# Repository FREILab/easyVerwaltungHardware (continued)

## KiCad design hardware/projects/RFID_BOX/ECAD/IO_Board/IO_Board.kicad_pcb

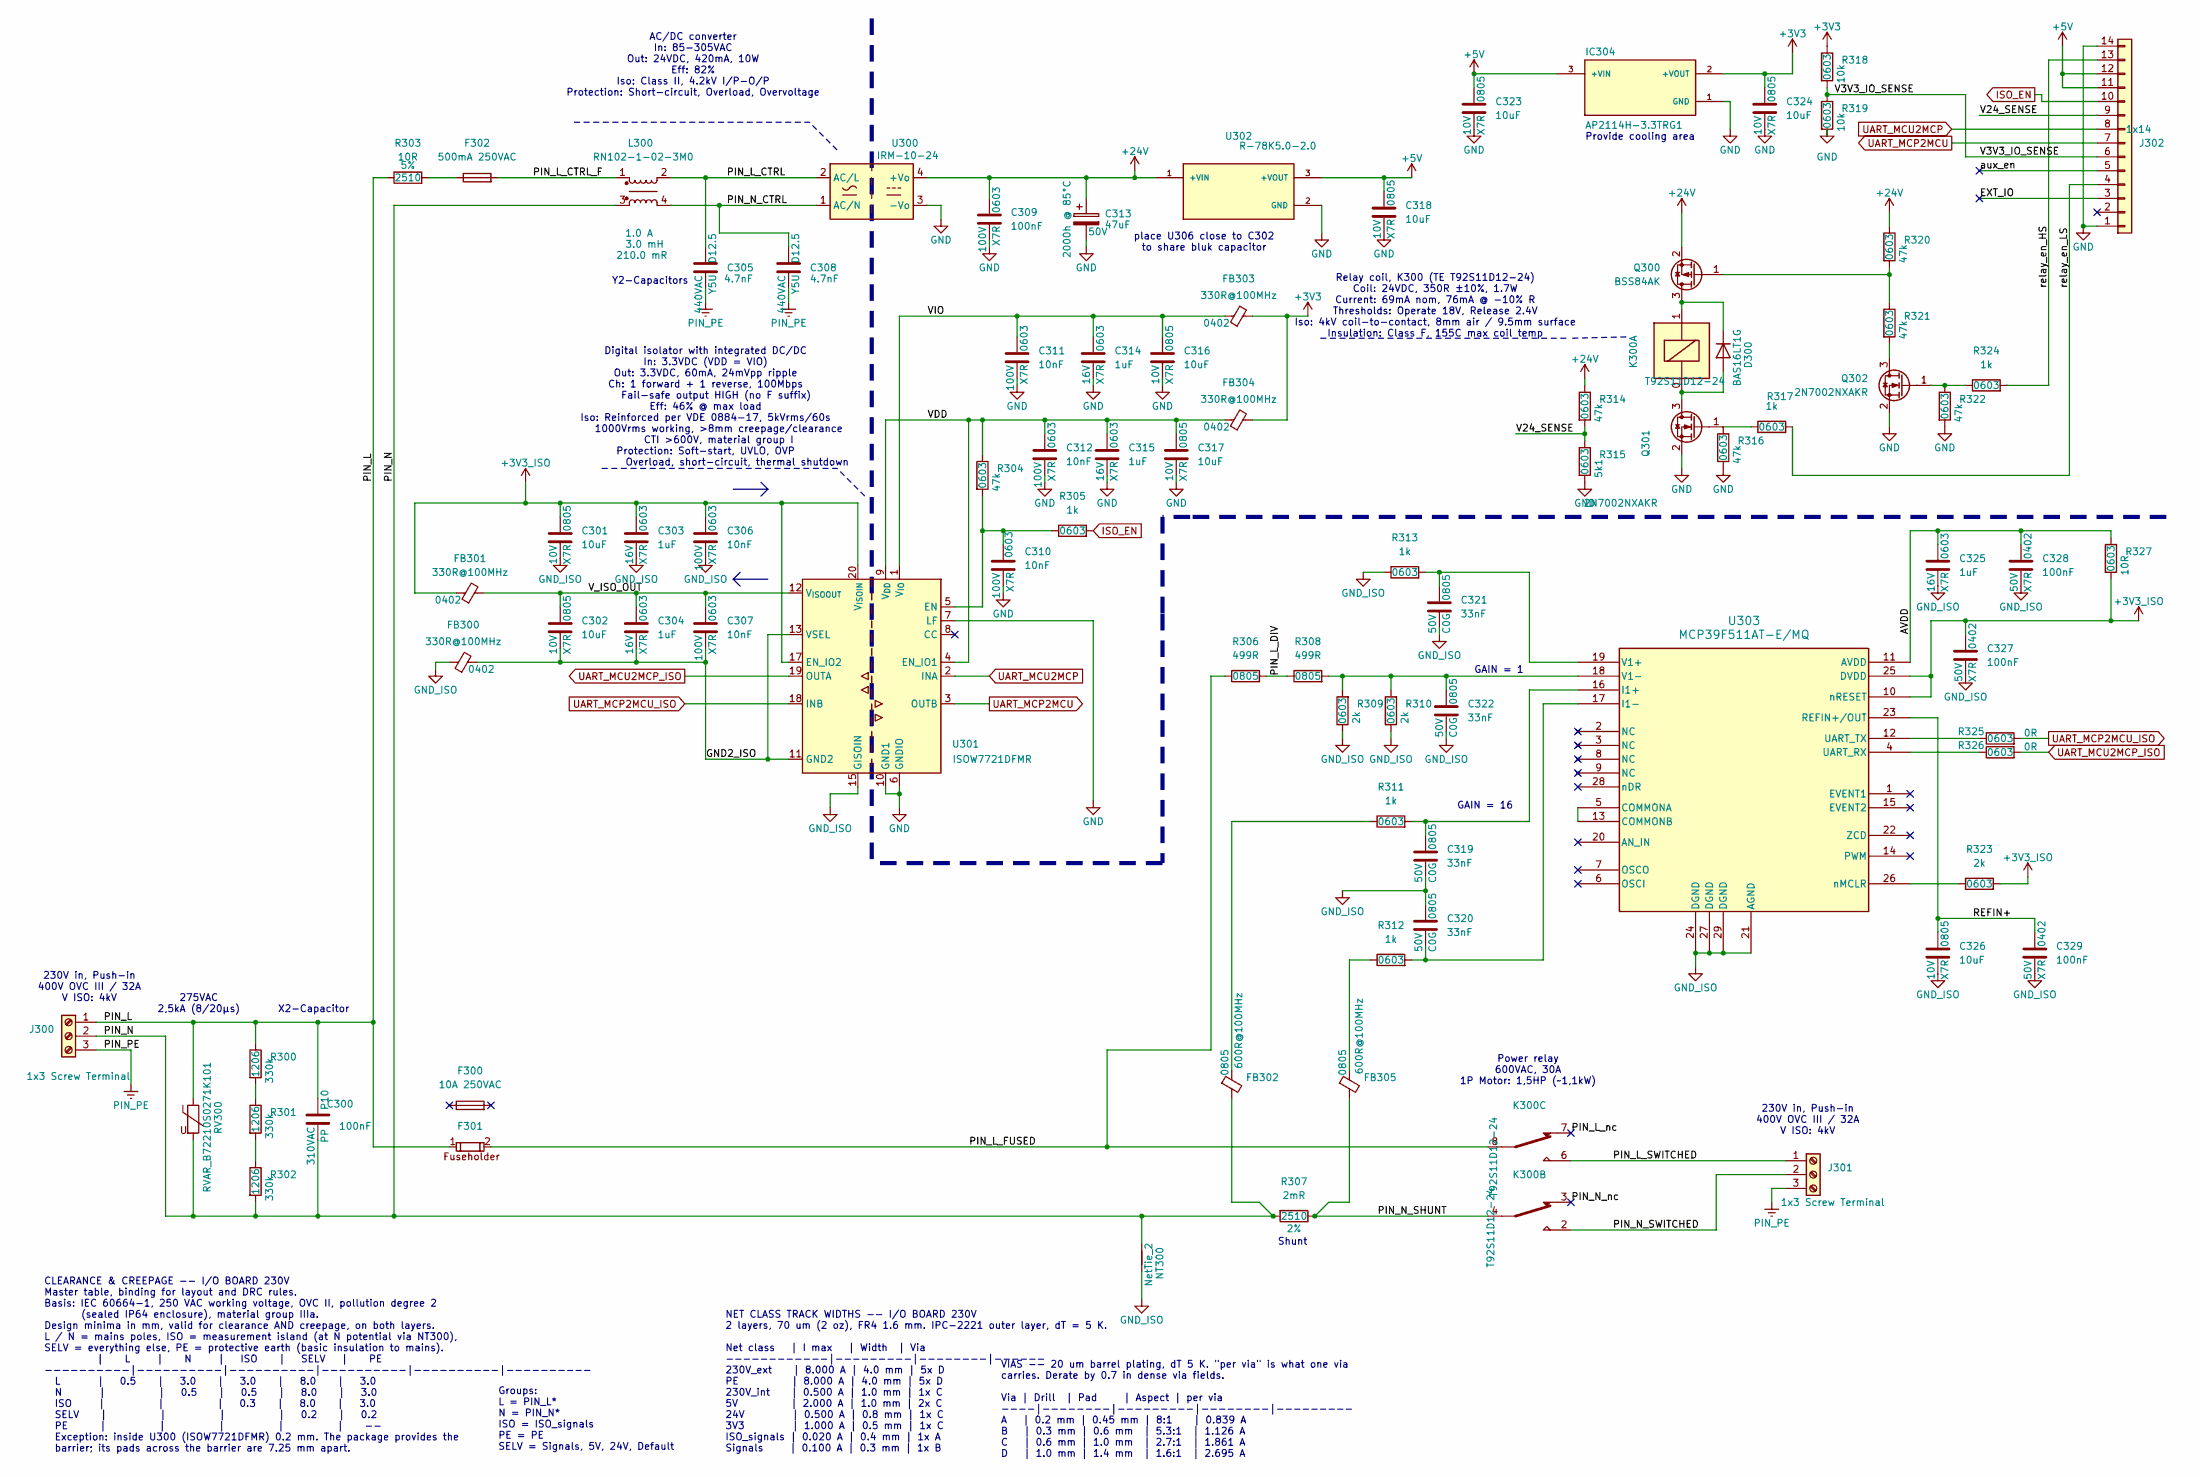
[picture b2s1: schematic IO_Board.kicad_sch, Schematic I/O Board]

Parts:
C300: 100nF; C_Wurth_WCAP-FTXX-P10L13W7H13; Voltage Rating 310VAC; Manufacturer Part Number 890334023023CS
C301, C302, C316, C317, C318, C323, C324, C326: 10uF; C_0805_2012Metric; Voltage Rating 10V; Manufacturer Part Number CC0805KFX7R6BB106
C303, C304, C314, C315, C325: 1uF; C_0603_1608Metric; Voltage Rating 16V; Manufacturer Part Number CGA3E1X7R1C105K080AC
C305, C308: 4.7nF; C_Disc_D12.5mm_W5.0mm_P7.50mm; Voltage Rating 440VAC; Manufacturer Part Number VY2472M49Y5US63L7
C306, C307, C310, C311, C312: 10nF; C_0603_1608Metric; Voltage Rating 100V; Manufacturer Part Number GRM188R72A103KA01D
C309: 100nF; C_0603_1608Metric; Voltage Rating 100V; Manufacturer Part Number 885012206120
C313: 47uF; CP_Radial_D6.3mm_H11.0mm_P2.50mm; Voltage Rating 50V; Manufacturer Part Number 860010673012
C319, C320, C321, C322: 33nF; C_0805_2012Metric; Voltage Rating 50V; Manufacturer Part Number GRM2165C1H333JA01J
C327, C328, C329: 100nF; C_0402_1005Metric; Voltage Rating 50V; Manufacturer Part Number GCM155R71H104KE02J
D300: BAS16LT1G; SOT-23; Manufacturer Part Number BAS16LT1G
F300: 10A 250VAC; Voltage Rating 250VAC; Manufacturer Part Number 5HT 10-R
F301: F_696309001002; F_Wurth_WR-FSH_696309001002; Manufacturer Part Number 696309001002
F302: 500mA 250VAC; F_MRT_BEL; Voltage Rating 250VAC; Manufacturer Part Number MRT 500-BULK
FB300, FB301, FB303, FB304: 330R@100MHz; L_0402_1005Metric; Manufacturer Part Number BLM15EX331SN1D
FB302, FB305: 600R@100MHz; L_0805_2012Metric; Manufacturer Part Number MH2029-601Y
IC304: AP2114H-3.3TRG1; SOT-223-3_TabPin2; Manufacturer Part Number AP2114H-3.3TRG1
J300, J301: 1x3 Screw Terminal; J_2604-1103_WAG; Manufacturer Part Number 2604-1103
J302: 1x14; J_01x14_SFW14S-2STE1LF; Manufacturer Part Number SFW14S-2STE1LF
K300: T92S11D12-24; K_T92S11D12-24; Manufacturer Part Number T92S11D12-24
L300: RN102-1-02-3M0; L_RN102_SCN; Manufacturer Part Number RN102-1-02-3M0
NT300: NetTie_2
Q300: BSS84AK; SOT-23; Manufacturer Part Number BSS84AK,215
Q301, Q302: 2N7002NXAKR; SOT-23; Manufacturer Part Number 2N7002NXAKR
R300, R301, R302: 330k; R_1206_3216Metric; Tolerance 1%; Manufacturer Part Number CRCW1206330KFKEAHP
R303: 10R; R_Axial_DIN0207_L6.3mm_D2.5mm_P15.24mm_Horizontal; Tolerance 5%; Manufacturer Part Number PR01000101009JA500
R304, R314, R316, R320, R321, R322: 47k; R_0603_1608Metric; Tolerance 1%; Manufacturer Part Number CRCW060347K0FKEAC
R305, R311, R312, R313, R317, R324: 1k; R_0603_1608Metric; Tolerance 1%; Manufacturer Part Number CRCW06031K00FKEAC
R306, R308: 499R; R_0805_2012Metric; Tolerance 1%; Manufacturer Part Number CRCW0805499RFKEAC
R307: 2mR; R_2512_CSI2H-2512K-2L00G; Tolerance 2%; Manufacturer Part Number CSI2H-2512K-2L00G
R309, R310, R323: 2k; R_0603_1608Metric; Tolerance 1%; Manufacturer Part Number CRCW06032K00FKEAC
R315: 5k1; R_0603_1608Metric; Tolerance 1%; Manufacturer Part Number CRCW06035K10FKEA
R318, R319: 10k; R_0603_1608Metric; Tolerance 1%; Manufacturer Part Number CRCW060310K0FKEAC
R325, R326: 0R; R_0603_1608Metric; Tolerance 1%; Manufacturer Part Number CRCW06030000Z0EBC
R327: 10R; R_0603_1608Metric; Tolerance 1%; Manufacturer Part Number CRCW060310R0FKEA
RV300: RVAR_B72210S0271K101; RV_Disc_D12mm_W5.1mm_P7.5mm; Manufacturer Part Number B72210S0271K101
U300: IRM-10-24; IC_IRM-10-24_THT; Manufacturer Part Number IRM-10-24
U301: ISOW7721DFMR; SOIC-20W_7.5x12.8mm_P1.27mm; Manufacturer Part Number ISOW7721DFMR
U302: R-78K5.0-2.0; IC_CONV_R-78K5.0-2.0; Manufacturer Part Number R-78K5.0-2.0
U303: MCP39F511AT-E/MQ; IC_QFN28_MQ_MCH; Manufacturer Part Number MCP39F511AT-E/MQ

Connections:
+3V3: C324.1, FB303.2, FB304.2, IC304.2 (+VOUT), R318.1
+3V3_ISO: C301.1, C303.1, C306.1, C327.1, FB301.1, R323.2, R327.2, U301.17 (EN_IO2), U301.20 (V_{ISOIN}), U303.10 (nRESET), U303.25 (DVDD)
+5V: C318.1, C323.1, IC304.3 (+VIN), J302.11, J302.12, U302.3 (+VOUT)
+24V: C309.1, C313.1, Q300.2 (S), R314.1, R320.1, U300.4 (+Vo), U302.1 (+VIN)
/AVDD: C325.1, C328.1, R327.1, U303.11 (AVDD)
/EXT_IO: J302.3
/GND2_ISO: C302.2, C304.2, C307.2, FB300.2, U301.11 (GND2), U301.13 (VSEL)
/PIN_L: C300.1, F301.1, J300.1, J300.4, R300.1, R303.1, RV300.1
/PIN_L_CTRL: C305.1, L300.2, U300.2 (AC/L)
/PIN_L_CTRL_F: F302.2, L300.1
/PIN_L_DIV: R306.2, R308.1
/PIN_L_FUSED: F301.2, K300.8, R306.1
/PIN_L_SWITCHED: J301.1, J301.4, K300.6
/PIN_L_nc: K300.7
/PIN_L_nc_1: K300.7
/PIN_N: C300.2, FB302.2, J300.2 (Pin_3), J300.5, L300.3, NT300.2, R302.2, R307.2, RV300.2
/PIN_N_CTRL: C308.1, L300.4, U300.1 (AC/N)
/PIN_N_SHUNT: FB305.2, K300.4, R307.1
/PIN_N_SWITCHED: J301.2 (Pin_3), J301.5, K300.2
/PIN_N_nc: K300.3
/PIN_N_nc_1: K300.3
/REFIN+: C326.1, C329.1, U303.23 (REFIN+/OUT)
/V3V3_IO_SENSE: J302.6, R318.2, R319.1
/V24_SENSE: J302.9, R314.2, R315.1
/VDD: C312.1, C315.1, C317.1, FB304.1, R304.1, U301.4 (EN_IO1), U301.9 (V_{DD})
/VIO: C311.1, C314.1, C316.1, FB303.1, U301.1 (V_{IO})
/V_ISO_OUT: C302.1, C304.1, C307.1, FB301.2, U301.12 (V_{ISOOUT})
/aux_en: J302.5
/relay_en_HS: J302.13, R324.2
/relay_en_LS: J302.4, R317.2
GND: C309.2, C310.2, C311.2, C312.2, C313.2, C314.2, C315.2, C316.2, C317.2, C318.2, C323.2, C324.2, IC304.1 (GND), J302.1, J302.14, Q301.2 (S), Q302.2 (S), R315.2, R316.2, R319.2, R322.2, U300.3 (-Vo), U301.6 (GNDIO), U301.7 (LF), U301.10 (GND1), U302.2 (GND)
GND_ISO: C301.2, C303.2, C306.2, C319.2, C320.1, C321.2, C322.2, C325.2, C326.2, C327.2, C328.2, C329.2, FB300.1, NT300.1, R309.1, R310.1, R313.1, U301.15 (GISOIN), U303.21 (AGND), U303.24 (DGND), U303.27 (DGND), U303.29 (DGND)
ISO_EN: J302.10, R305.2
unnamed: D300.1 (A), K300.0, Q301.3 (D)
unnamed: D300.3 (K), K300.1, Q300.3 (D)
unnamed: F302.1, R303.2
unnamed: FB302.1, R311.1
unnamed: FB305.1, R312.1
unnamed: Q300.1 (G), R320.2, R321.1
unnamed: Q301.1 (G), R316.1, R317.1
unnamed: Q302.3 (D), R321.2
unnamed: Q302.1 (G), R322.1, R324.1
unnamed: R300.2, R301.1
unnamed: R301.2, R302.1
unnamed: C310.1, R304.2, R305.1, U301.5 (EN)
unnamed: U303.5 (COMMONA), U303.13 (COMMONB)
unnamed: C319.1, R311.2, U303.16 (I1+)
unnamed: C320.2, R312.2, U303.17 (I1-)
unnamed: R326.1, U303.4 (UART_RX)
unnamed: R325.1, U303.12 (UART_TX)
unnamed: C321.1, R313.2, U303.19 (V1+)
unnamed: C322.1, R308.2, R309.2, R310.2, U303.18 (V1-)
unnamed: R323.1, U303.26 (nMCLR)
PIN_PE: C305.2, C308.2, J300.3, J300.6, J301.3, J301.6
UART_MCP2MCU: J302.7, U301.3 (OUTB)
UART_MCP2MCU_ISO: R325.2, U301.18 (INB)
UART_MCU2MCP: J302.8, U301.2 (INA)
UART_MCU2MCP_ISO: R326.2, U301.19 (OUTA)

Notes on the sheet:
VIAS -- 20 um barrel plating, dT 5 K. "per via" is what one via carries. Derate by 0.7 in dense via fields. Via | Drill | Pad | Aspect | per via ----|--------|---------|--------|--------- A | 0.2 mm | 0.45 mm | 8:1 | 0.839 A B | 0.3 mm | 0.6 mm | 5.3:1 | 1.126 A C | 0.6 mm | 1.0 mm | 2.7:1 | 1.861 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
230V in, Push-in 400V OVC III / 32A V ISO: 4kV
Groups: L = PIN_L* N = PIN_N* ISO = ISO_signals PE = PE SELV = Signals, 5V, 24V, Default
NET CLASS TRACK WIDTHS -- I/O BOARD 230V 2 layers, 70 um (2 oz), FR4 1.6 mm. IPC-2221 outer layer, dT = 5 K. Net class | I max | Width | Via ------------|---------|--------|------ 230V_ext | 8.000 A | 4.0 mm | 5x D PE | 8.000 A | 4.0 mm | 5x D 230V_int | 0.500 A | 1.0 mm | 1x C 5V | 2.000 A | 1.0 m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
place U306 close to C302 to share bluk capacitor
Y2-Capacitors
AC/DC converter In: 85-305VAC Out: 24VDC, 420mA, 10W Eff: 82% Iso: Class II, 4.2kV I/P-O/P Protection: Short-circuit, Overload, Overvoltage
Power relay 600VAC, 30A 1P Motor: 1,5HP (~1,1kW)
Digital isolator with integrated DC/DC In: 3.3VDC (VDD = VIO) Out: 3.3VDC, 60mA, 24mVpp ripple Ch: 1 forward + 1 reverse, 100Mbps Fail-safe output HIGH (no F suffix) Eff: 46% @ max load Iso: Reinforced per VDE 0884-17, 5kVrms/60s 1000Vrms working, >8mm creepage/clearance CTI >600V, material group I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
275VAC 2,5kA (8/20µs)
CLEARANCE & CREEPAGE -- I/O BOARD 230V Master table, binding for layout and DRC rules. Basis: IEC 60664-1, 250 VAC working voltage, OVC II, pollution degree 2 (sealed IP64 enclosure), material group IIIa. Design minima in mm, valid for clearance AND creepage, on both layers. L / N = mains poles, IS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
GAIN = 16
Relay coil, K300 (TE T92S11D12-24) Coil: 24VDC, 350R ±10%, 1.7W Current: 69mA nom, 76mA @ -10% R Thresholds: Operate 18V, Release 2.4V Iso: 4kV coil-to-contact, 8mm air / 9.5mm surface Insulation: Class F, 155C max coil temp
Shunt
GAIN = 1
Provide cooling area
X2-Capacitor

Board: 2 copper layers, 82 parts (0 on the bottom side), 52 nets, no tracks yet.

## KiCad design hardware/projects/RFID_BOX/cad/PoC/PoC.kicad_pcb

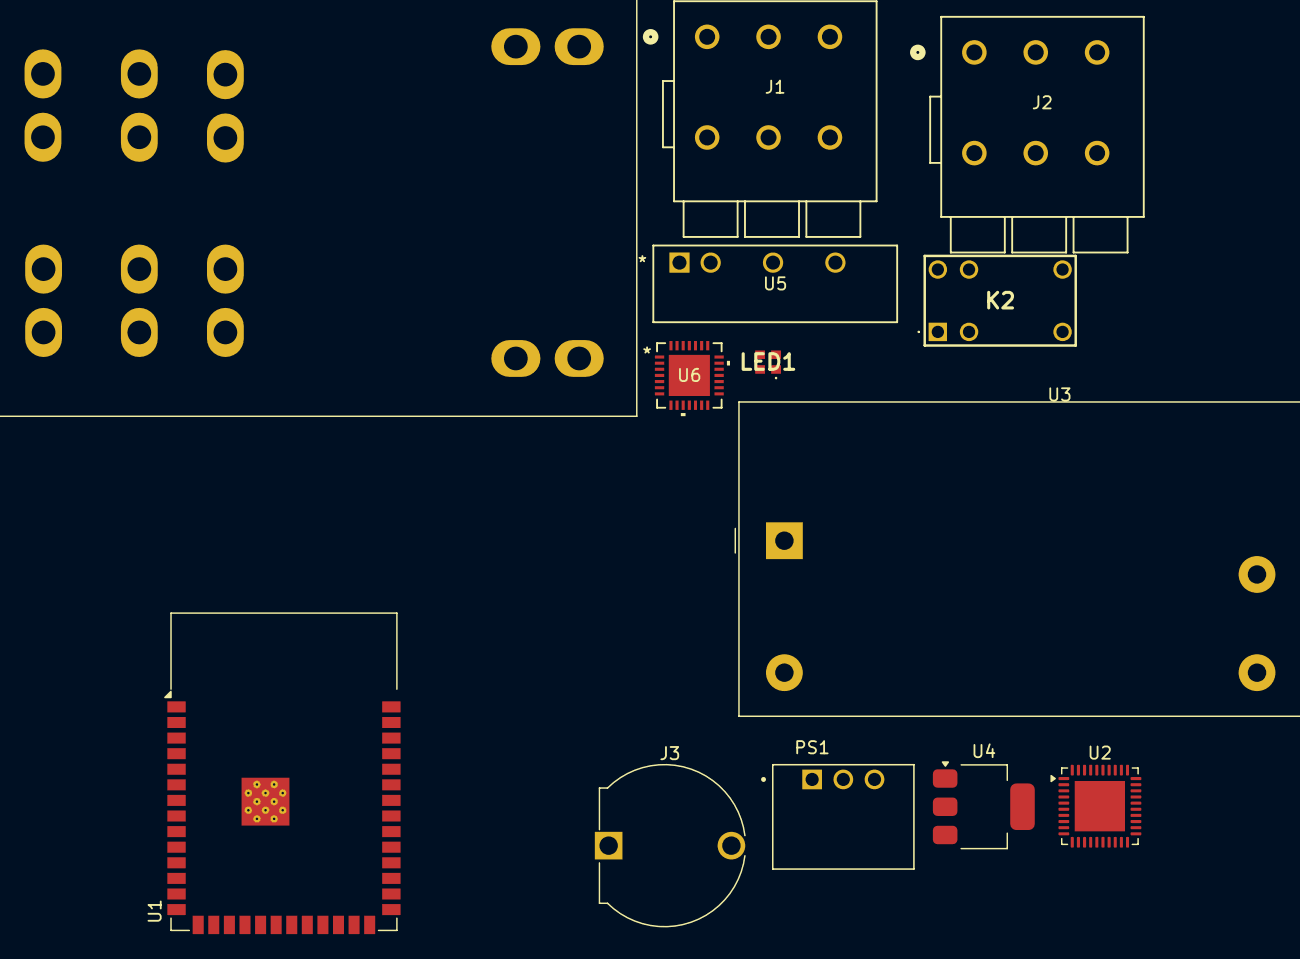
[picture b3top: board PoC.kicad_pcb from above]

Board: 2 copper layers, 13 parts (0 on the bottom side), 9 nets, no tracks yet.

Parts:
J1, J2: J_WAGO_2604-1103; J_2604-1103_WAG
J3: F_696309001002; F_Wurth_WR-FSH_696309001002
K1: T92S11D12-24; K_T92S11D12-24
K2: K_G5V-1-2_DC24
LED1: LED_IN-PI20TATPRPGPB; LED_INPI20TATPRPGPB
PS1: IC_R-78K5.0-2.0; IC_CONV_R-78K5.0-2.0
U1: ESP32-S3-WROOM-1
U2: PN5321A3HN_C1xx; HVQFN-40-1EP_6x6mm_P0.5mm_EP4.1x4.1mm
U3: IC_IRM-10-24; IC_IRM-10-24_THT
U4: AMS1117-3.3; SOT-223-3_TabPin2
U5: IC_RFB-0505S
U6: MCP39F511A-E/MQ; IC_QFN28_MQ_MCH

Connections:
unnamed: J1.1, J1.2
unnamed: J1.3, J1.4
unnamed: J1.5, J1.6
unnamed: J2.1, J2.2
unnamed: J2.3, J2.4
unnamed: J2.5, J2.6
unnamed: K2.5, K2.6
unnamed: U1.1 (GND), U1.40 (GND), U1.41 (GND)
unnamed: U2.11 (AVSS), U2.41 (AVSS)

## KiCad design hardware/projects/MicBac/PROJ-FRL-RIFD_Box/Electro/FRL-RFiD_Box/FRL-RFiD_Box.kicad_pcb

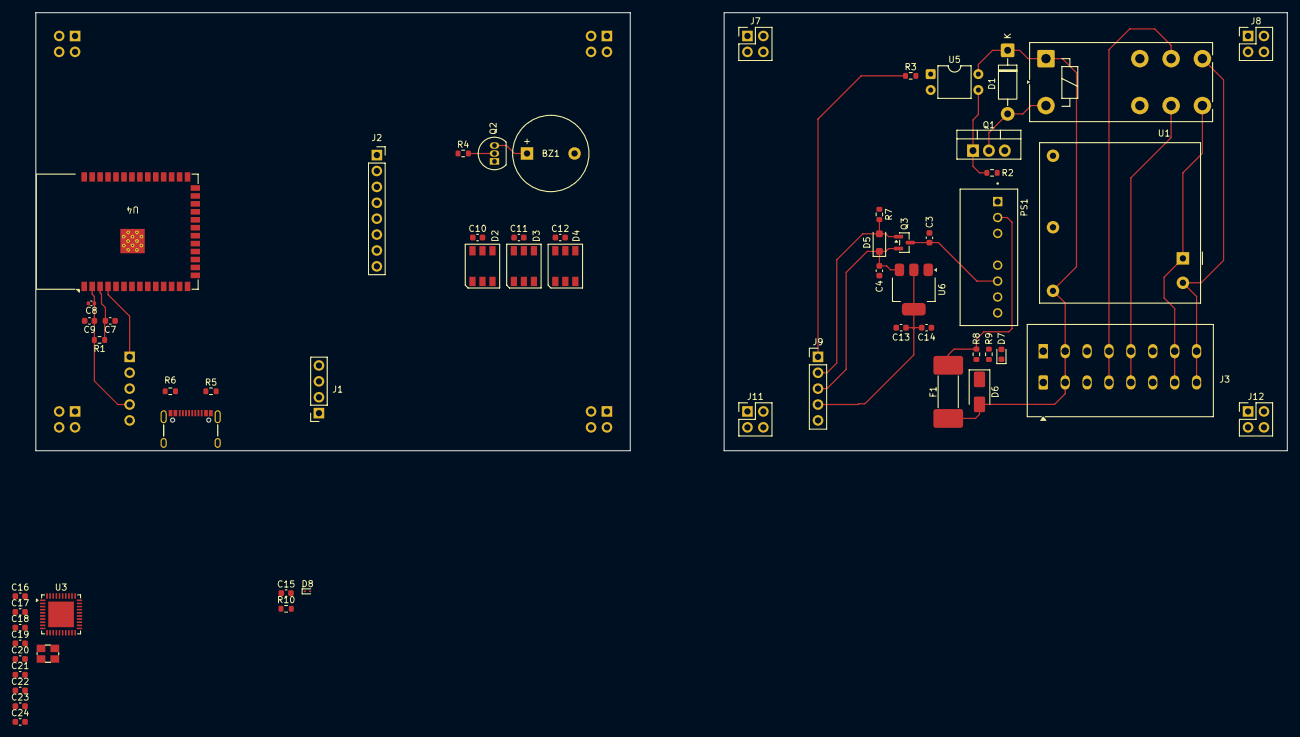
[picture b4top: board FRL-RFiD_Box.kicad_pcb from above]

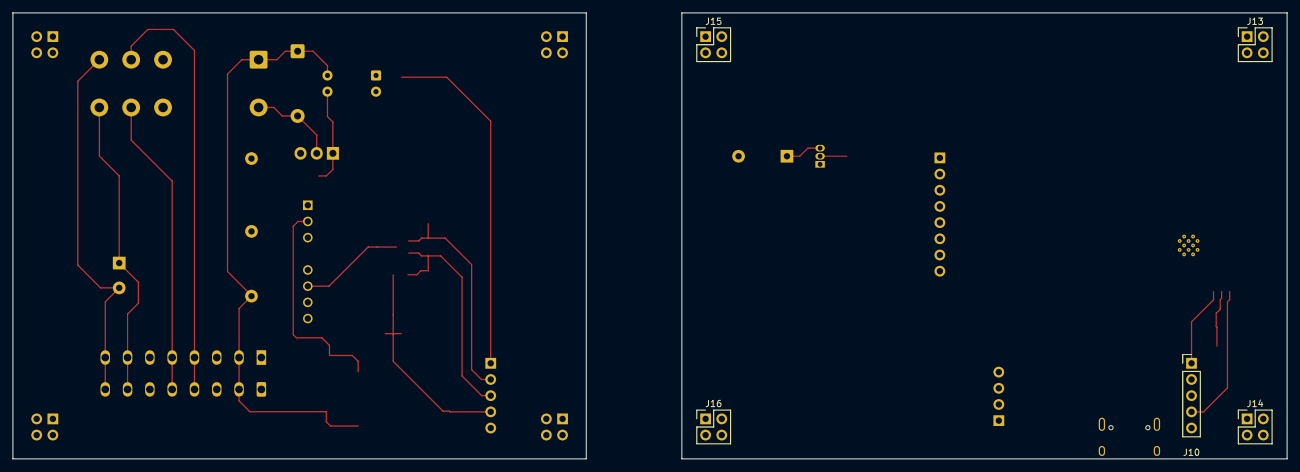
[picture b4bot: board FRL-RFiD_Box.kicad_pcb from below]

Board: 2 copper layers, 200.0 x 70.0 mm, 65 parts (5 on the bottom side), 44 nets.

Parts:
BZ1: TMB12A05; Buzzer_12x9.5RM7.6
C3, C4, C9, C16, C19: 10u; C_0603_1608Metric
C7, C15: 1u; C_0603_1608Metric
C8: 0.1u; C_0402_1005Metric
C10, C11, C12: 0.1uF; C_0603_1608Metric
C13: 22u Tantal or Elko; C_0603_1608Metric
C14, C17, C18, C20, C21: 100n; C_0603_1608Metric
C22: 4,7u; C_0603_1608Metric
C23, C24: 22p; C_0603_1608Metric
D1: 1N4007; D_DO-41_SOD81_P10.16mm_Horizontal
D2, D3, D4: WS2812; LED_WS2812_PLCC6_5.0x5.0mm_P1.6mm
D5: MBR120VLSF; D_SOD-123F
D6: SMAJ36CA; D_SMA
D7: LED G; LED_0603_1608Metric
D8: ESD9B3.3ST5G; D_SOD-923
F1: 200mA T; Fuse_Schurter_UMZ250
J1: I2C_OLED; PinSocket_1x04_P2.54mm_Vertical
J2: SPI_NFC; PinSocket_1x08_P2.54mm_Vertical
J3: WAGO (230V + 24V); TerminalBlock_WAGO_2601-1108_1x08_P3.50mm_Horizontal
J5: USB_C_Receptacle; USB-C_16
J7, J8, J11, J12, J13, J14, J15, J16: Conn_02x02_Odd_Even; PinHeader_2x02_P2.54mm_Vertical
J9, J10: Conn_01x05; PinHeader_1x05_P2.54mm_Vertical
K1: FINDER-41.52.9.024.4311; Relay_DPDT_Finder_40.52
PS1: RS6-2405S; CONV_RS6-2405S
Q1: IRLZ44N; TO-220-3_Vertical
Q2: BC547; TO-92_Inline
Q3: DMG2305UX; SOT-23
R1, R2, R10: 10k; R_0603_1608Metric
R3: 220; R_0603_1608Metric
R4: 1k; R_0603_1608Metric
R5, R6: 5,1k; R_0603_1608Metric
R7: 22k; R_0603_1608Metric
R8, R9: 2k2; R_0603_1608Metric
U1: RAC05-24SK; Converter_ACDC_RECOM_RAC05-xxSK_THT
U3: PN5321A3HN_C1xx; HVQFN-40-1EP_6x6mm_P0.5mm_EP4.1x4.1mm
U4: ESP32-S3-WROOM-1
U5: PC817; DIP-4_W7.62mm
U6: AMS1117-3.3; SOT-223-3_TabPin2
Y1: 27.12MHz; Crystal_SMD_3.2x2.5mm

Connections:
24_GND: D6.1 (A1), D7.1 (K), J3.1, PS1.1 (-VIN), Q1.3 (S), R2.2, U1.4 (-Vout)
+3V3: C8.1, C9.1, J1.4, J2.5, J10.4, R1.2, R10.2, U4.2 (3V3)
+3V3 Bot: C13.1, C14.1, J9.4, U6.2 (VO)
+5V: C10.2, C11.2, C12.2, D2.3 (VCC), D2.5 (VDD), D3.3 (VCC), D3.5 (VDD), D4.3 (VCC), D4.5 (VDD), J10.3, Q2.1 (C)
+5V Bot: C4.1, D5.1 (K), J9.3, Q3.2 (S), U6.3 (VI)
/230V_AC_FINDER_L (OUT): J3.5, K1.21
/230V_AC_FINDER_N (OUT): J3.4, K1.11
/230V_AC_RAC05_L (IN): J3.7, K1.24, U1.1 (AC(L))
/230V_AC_RAC05_N (IN): J3.8, K1.14, U1.2 (AC(N))
/+5V_RS6-2405S_+VOUT: C3.1, PS1.6 (+VOUT), Q3.3 (D)
/+24V_RAC05_OUT: D1.1 (K), D6.2 (A2), F1.1, J3.2, K1.A1, U1.5 (+Vout), U5.4
/+24V_RS6_+VIN: F1.2, PS1.2 (+VIN), R8.1
/BUZZER: R4.1, U4.33 (IO40)
/EN: C7.1, R1.1, U4.3 (EN)
/ESP_IO_0: C15.1, D8.2 (A2), R10.1, U4.27 (IO0)
/I2C_OLED_SCL: J1.1, U4.17 (IO9)
/I2C_OLED_SDA: J1.2, U4.12 (IO8)
/PC817 (OPT): J10.1, U4.4 (IO4)
/PC817 (OPT) Bot: J9.1, R3.1
/SPI_NFC_IRQ: J2.7, U3.25 (P70_IRQ), U4.18 (IO10)
/SPI_NFC_MISO: J2.2, U3.29 (MISO/P71), U4.21 (IO13)
/SPI_NFC_MOSI: J2.3, U3.28 (MOSI/SDA/HSU_TX), U4.20 (IO12)
/SPI_NFC_SCK: J2.1, U3.30 (SCK/P72), U4.22 (IO14)
/SPI_NFC_SS: J2.4, U3.27 (NSS/P50_SCL/HSU_RX), U4.19 (IO11)
/USB_CC1: J5.A5 (CC1), R6.1
/USB_CC2: J5.B5 (CC2), R5.1
/USB_D+: J5.A6 (D+), J5.B6 (D+), U4.14 (USB_D+)
/USB_D-: J5.A7 (D-), J5.B7 (D-), U4.13 (USB_D-)
/VBUS: C16.1, J5.VBUS, J10.2
/VBUS Bot: D5.2 (A), J9.2, Q3.1 (G), R7.1
/WS2812: D2.2 (DIN), U4.5 (IO5)
GND: BZ1.2 (-), C3.2, C4.2, C7.2, C8.2, C9.2, C10.1, C11.1, C12.1, C13.2, C14.2, C15.2, C16.2, C17.2, C18.2, C19.2, C20.2, C21.2, C22.2, C23.2, C24.2, D2.6 (VSS), D3.6 (VSS), D4.6 (VSS), D8.1 (A1), J1.3, J2.6, J5.GND, J5.S (SHIELD), J9.5, J10.5, PS1.7 (-VOUT), R5.2, R6.2, R7.2, U3.1 (DVSS), U3.3 (TVSS1), U3.7 (TVSS2), U3.11 (AVSS), U3.18 (TESTEN), U3.41 (AVSS), U4.1 (GND), U4.40 (GND), U4.41 (GND), U5.2, U6.1 (GND)
unnamed: BZ1.1 (+), Q2.3 (E)
unnamed: D1.2 (A), K1.A2, Q1.2 (D)
unnamed: D2.1 (DOUT), D3.2 (DIN)
unnamed: D3.1 (DOUT), D4.2 (DIN)
unnamed: D7.2 (A), R9.2
unnamed: Q1.1 (G), R2.1, U5.3
unnamed: Q2.2 (B), R4.2
unnamed: R3.2, U5.1
unnamed: R8.2, R9.1
unnamed: C17.1, C18.1, C19.1, C20.1, C21.1, C22.1, U3.5 (TVDD), U3.8 (AVDD), U3.23 (PVDD), U3.39 (DVDD)
unnamed: C23.1, U3.14 (OSCIN), Y1.1
unnamed: C24.1, U3.15 (OSCOUT), Y1.2

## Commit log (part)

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2026-03-01 initial_commit
2026-03-01 move file
2026-03-01 fix typo
2026-03-01 fix intro
2026-03-01 try fix autobuild
2026-03-01 test
2026-03-01 prep tags
2026-03-01 ready for tag
2026-03-01 minor edit
2026-03-01 improve settings and secrets
2026-03-08 clea up comments. code run previosly
2026-03-08 Update Doxyfile project information and input sources
2026-03-08 add to ignore
2026-03-08 Add GitHub Actions workflow for documentation deployment
2026-03-08 add doxy group
2026-03-08 update doxy
2026-04-24 Back to a working state
2026-04-24 tet sucessfull
2026-04-24 update example
2026-04-26 tested, was sucessful, ready to tag
2026-04-30 Baseline OTA implemetation
2026-04-30 Added README and option to set new credentials in secret.h
2026-05-04 Updated Folderstructure and doc
2026-05-05 easyVerwaltung API lib
2026-05-05 minor updates
2026-05-11 Update configuration files and documentation for RFIDBOX project
2026-05-11 Update secret and platformio configuration files for improved clarity and security
2026-05-11 Update backend communication details in secret.h.example for clarity
2026-05-11 Refactor device pairing configurations for clarity and consistency
2026-05-12 Refactor server configuration and enhance logging for authentication processes;
    now working RFID
2026-05-12 Add OTA support with conditional compilation and logging
    all working
2026-05-12 Add workspace configuration for RFIDBOX_PoC project
2026-05-12 started door
2026-05-12 Remove door pair configurations and associated build environments from platformio.ini
2026-05-12 compiliert
2026-05-14 Umbenennung aller Projektordner auf konsistente Namen: - RFIDBOX_PoC → RFID_BOX_legacy - RFIDBOX_Easy → RFID_BOX_easyVerwaltung - RFID_Door_Poc → DOOR_legacy - MachineNodes → MachineNode - RFIDBOX_Po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
    Neuer leerer Projektordner DOOR_easyVerwaltung angelegt (Arduino Uno R4
    WiFi, easyVerwaltung-API, steht noch aus).
    secret.h / secret.h.example vereinheitlicht: WiFi-Credentials nur noch
    in platformio.secrets.ini, nicht doppelt in secret.h. SERVER_HOST statt
    SERVER_IP in allen Projekten.
2026-05-14 Remove unnecessary .gitignore files from door and RFID projects
2026-05-14 remove builds
2026-05-14 auto ignores
2026-05-14 minor changes
2026-05-14 minor fix
2026-05-15 Refactor DOOR project for WiFi support: update platform and board settings, remove Ethernet fallback, and add OTA upload functionality.
2026-05-15 geht im groben
2026-05-15 OTA working
2026-05-15 Add timeout configurations and non-blocking WiFi reconnect logic
2026-05-15 Add watchdog timer support and WiFi reconnect interval configuration
2026-05-15 Refactor UID handling and improve OTA upload response handling
2026-05-15 Refactor deployment configurations and add OTA upload support for multiple environments
2026-05-15 Fix WiFi password definition and update authentication token variable name
2026-05-15 Fix server hostname definition in secret.h.example
2026-05-15 Add 24/7 stability review and improvement recommendations for LASERSAUR_HMI_legacy and RFID_BOX components
2026-05-16 Add Smart Terminal 3D-Print configuration and services setup
2026-05-16 start sceleton
2026-05-17 clean start
2026-05-17 start structure
2026-05-17 compiled
2026-05-17 Refactor project structure: update CMakeLists, add new tasks, and implement blinking functionality
2026-05-17 compiled, läuft
2026-05-17 envs festgelegt, compiled und flashed
2026-05-17 progress
2026-05-17 Update deployment tasks and documentation for USB and OTA methods
2026-05-17 umstieg auf esp32
2026-05-17 Refactor settings and main logic for improved readability and maintainability
2026-05-17 Add server keepalive functionality and update button pin to resolve conflict
2026-05-18 neue pio-env's fuer lasercutterxtool
2026-05-19 Update platformio configurations and add health check functionality for xtool integration
2026-05-19 Add easyAPI library for backend communication
    - Introduced `easyAPI` as a small embedded C library for backend communication in firmware projects.
    - Implemented core functionalities including health checks, login, and heartbeat requests.
    - Added CMake configuration for building the library, tests, and examples.
    - Created example applications demonstrating usage of the API in various modes (single login, heartbeat login, etc.).
    - Included a service layer for non-blocking operations and event handling.
    - Added scripts for running tests and generating coverage reports.
2026-05-19 Add README files for easyVerwaltung projects and legacy counterparts
2026-05-19 start testing
2026-05-19 erstes lebenszeichen vom server
2026-05-19 debuggin rfid
2026-05-19 Update OTA Fleet Plan with current status, open issues, and testing roadmap
2026-05-20 Update .gitignore to include build artifacts for RFID_BOX_easyVerwaltung
2026-05-20 fix prusa xl
2026-05-24 Add Telnet server support and enhance logging in main.cpp
2026-05-24 Add Telnet server functionality and update logging to use TeeStream
2026-05-24 revert
2026-05-24 mehr debug sachen
2026-05-24 usb flash door geht wieder
2026-05-24 Add error JSON files and update WiFi connection logic in main.cpp
2026-05-24 not yet working, mostly network
2026-05-24 Add initial implementation for RFID door control system with OTA support
2026-05-24 Refactor firmware structure for RobotDyn UNO+WiFi R3: - Update README with hardware details and architecture overview. - Enhance platformio.ini for environment configurations. - Implement main logic 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
2026-05-25 Update README and platformio.ini to reflect DHCP IP address usage for OTA
2026-05-25 compiled und flashed
2026-05-25 deploy: e4b3981eeb9ada43625ffa4e166642beba625146
2026-05-25 beret für tests
2026-05-25 geht alles
2026-05-25 sollte jetzt passen, praktischer test
2026-05-25 funktioniert.
2026-05-25 Add ESP8266 WiFi modem functionality and integrate with ATmega
    - Implemented main functionality for ESP8266 to maintain WiFi connection and handle HTTP POST requests from ATmega.
    - Added Telnet debugging support and OTA updates via mDNS.
    - Created settings header for configurable parameters such as WiFi credentials and heartbeat intervals.
    - Introduced new functions for processing serial input, executing HTTP POST requests, and managing WiFi connections.
    - Added error handling for WiFi connection failures and server response codes.
    - Established communication protocol between ESP8266 and ATmega for heartbeat and data transmission.
2026-05-25 Update README files for various projects: add flashing and debugging instructions, clarify hardware details, and outline project status and API communication.
2026-05-25 Update README.md: Revise hardware overview and system architecture sections for clarity and completeness
2026-05-25 deploy: 56db210fe6f375ec91b751eadf4b23cb9ffa2d83
2026-05-25 Update README.md: Add details about onboard and external current sensor variants for machine hour tracking
2026-05-25 Update platformio.ini: Add missing line for build flags configuration
2026-05-27 wokwi diagram & config
2026-05-29 poc loki & improved wokwi
2026-06-05 Enhance network reliability: Implement WiFi stack reset after consecutive connection failures and ensure network services restart on reconnect
2026-06-15 Add debug logging and server health check functionality for improved diagnostics
2026-06-16 Increase buffer sizes in busDbg function for enhanced logging capabilities
2026-06-16 Refactor waitMotorOK function to accept LED state parameters and implement RFID debounce cooldown to prevent duplicate events
    -> läuft stabil und schnell
2026-06-17 Add debug message handling for ATMDBG in ESP module and enhance logging in ATmega
2026-06-17 Implement periodic health checks for RFID module and reinitialize if unresponsive
2026-06-27 add old files
